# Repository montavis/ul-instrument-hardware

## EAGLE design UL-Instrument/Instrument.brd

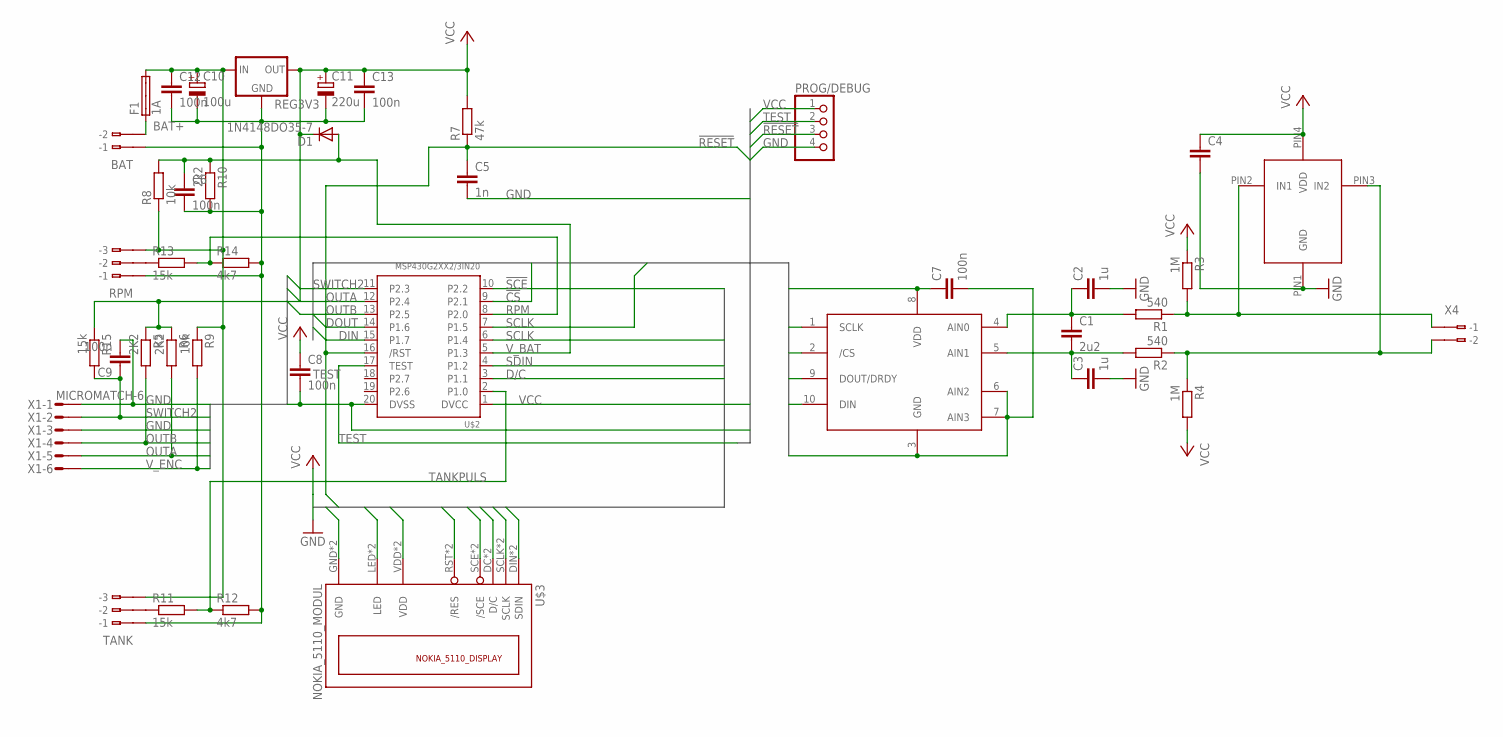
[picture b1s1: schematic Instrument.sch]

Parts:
BAT: 233-102
C1: 2u2; C025-050X050
C2, C3: 1u; C025-050X050
C4: C-EU025-050X050; C025-050X050
C5: 1n; C025-024X044
C6, C7, C8, C9, C12, C13: 100n; C025-050X050
C10: 100u; E5-8,5
C11: 220u; E5-8,5
D1: 1N4148DO35-7; DO35-7
F1: 1A; SHK20Q
PROG/DEBUG: PINHD-1X4; 1X04
R1, R2: 540; 0207/2V
R3, R4: 1M; 0207/2V
R5, R6: 2K2; 0207/2V
R7: 47k; 0204V
R8: 10k; 0204/5
R9: 10k; 0207/2V
R10: 2k2; 0204/5
R11, R13, R15: 15k; 0207/2V
R12, R14: 4k7; 0207/2V
REG3V3: 78MXXL
RPM: 233-103
TANK: 233-103
THERMO_ADC: ADS1118IDGST; MSOP10
U$1: TPD2E001DZDR; PDSO-G4
U$2: MSP430G2XX2/3IN20; DIL20
U$3: NOKIA_5110_MODUL; CHINA_N5110
X1: MICROMATCH-6
X4: 233-102

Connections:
!CS: THERMO_ADC.2 (/CS), U$2.9 (P2.1)
!RESET: C5.1, PROG/DEBUG.3, R7.1, U$2.16 (/RST), U$3.RST (/RES), U$3.RST2 (/RES)
!SCE: U$2.10 (P2.2), U$3.SCE (/SCE), U$3.SCE2 (/SCE)
BAT+: C10.+, C12.1, F1.2A, R8.1, R9.1, REG3V3.IN, RPM.B3 (B-3), TANK.B3 (B-3)
D/C: U$2.3 (P1.1), U$3.DC (D/C), U$3.DC2 (D/C)
DIN: THERMO_ADC.10 (DIN), U$2.15 (P1.7)
DOUT: THERMO_ADC.9 (DOUT/DRDY), U$2.14 (P1.6)
GND: BAT.B1 (B-1), C2.2, C3.2, C4.2, C5.2, C6.2, C7.2, C8.2, C9.2, C10.-, C11.-, C12.2, C13.2, PROG/DEBUG.4, R10.2, R12.2, R14.2, REG3V3.GND, RPM.B1 (B-1), TANK.B1 (B-1), THERMO_ADC.3 (GND), THERMO_ADC.6 (AIN2), THERMO_ADC.7 (AIN3), U$1.PIN1 (GND), U$2.20 (DVSS), U$3.GND, U$3.GND2 (GND), X1.1, X1.3
unnamed: C1.1, C2.1, R1.2, THERMO_ADC.4 (AIN0)
unnamed: C1.2, C3.1, R2.2, THERMO_ADC.5 (AIN1)
unnamed: R1.1, R3.2, U$1.PIN2 (IN1), X4.B1 (B-1)
unnamed: R2.1, R4.1, U$1.PIN3 (IN2), X4.B2 (B-2)
unnamed: BAT.B2 (B-2), F1.1A
unnamed: R13.1, RPM.B2 (B-2)
unnamed: R11.1, TANK.B2 (B-2)
OUTA: R6.2, U$2.12 (P2.4), X1.5
OUTB: R5.2, U$2.13 (P2.5), X1.4
RPM: R13.2, R14.1, U$2.8 (P2.0)
SCLK: THERMO_ADC.1 (SCLK), U$2.6 (P1.4), U$2.7 (P1.5), U$3.SCLK, U$3.SCLK2 (SCLK)
SDIN: U$2.4 (P1.2), U$3.DIN (SDIN), U$3.DIN2 (SDIN)
SWITCH2: C9.1, R15.2, U$2.11 (P2.3), X1.2
TANKPULS: R11.2, R12.1, U$2.2 (P1.0)
TEST: PROG/DEBUG.2, U$2.17 (TEST)
VCC: C4.1, C7.1, C8.1, C11.+, C13.1, D1.C, PROG/DEBUG.1, R3.1, R4.2, R5.1, R6.1, R7.2, R15.1, REG3V3.OUT, THERMO_ADC.8 (VDD), U$1.PIN4 (VDD), U$2.1 (DVCC), U$3.LED, U$3.LED2 (LED), U$3.VDD, U$3.VDD2 (VDD)
V_BAT: C6.1, D1.A, R8.2, R10.1, U$2.5 (P1.3)
V_ENC: R9.2, X1.6

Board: 2 copper layers, 41 parts (0 on the bottom side), 26 nets, no tracks yet.

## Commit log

2014-03-05 Bibliotheken hinzugefügt
